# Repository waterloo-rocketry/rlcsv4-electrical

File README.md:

# Remote Launch Control System V4

### Towerside Boards:

- **ground_launch_sequencer_board** Ground Launch Sequencer Board
- **relay_board** Relay Board, Used for valve actuation, ignition and tank heating

### Clientside Boards:

- **clientside_board** Clientside Board

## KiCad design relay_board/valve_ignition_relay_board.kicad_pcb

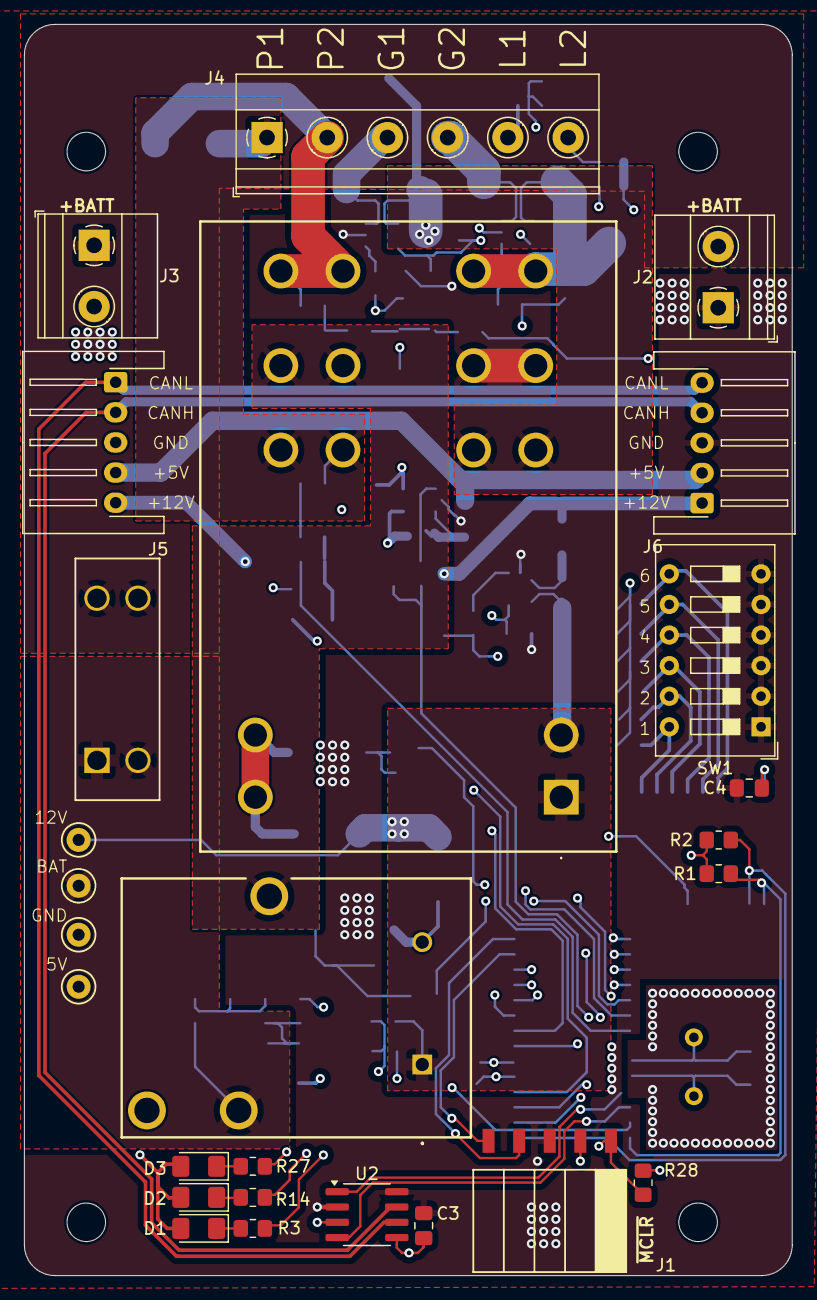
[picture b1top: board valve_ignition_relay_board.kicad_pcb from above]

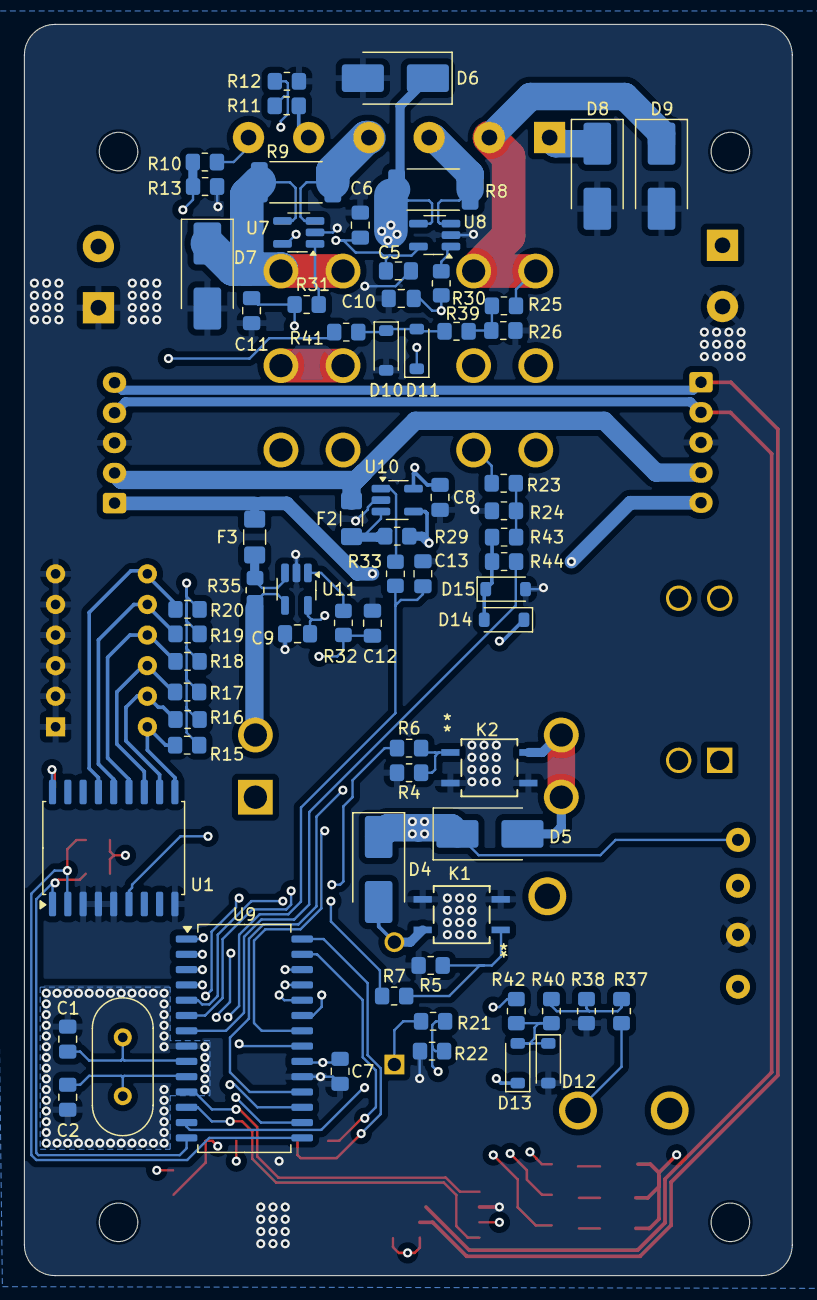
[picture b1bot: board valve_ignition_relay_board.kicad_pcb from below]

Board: 4 copper layers, 63.8 x 103.9 mm, 100 parts (70 on the bottom side), 68 nets.

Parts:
C1, C2: 27pF; C_0805_2012Metric_Pad1.18x1.45mm_HandSolder
C3: 10uF; C_0805_2012Metric_Pad1.18x1.45mm_HandSolder
C4, C5, C6, C7, C8, C9: 0.1uF; C_0805_2012Metric_Pad1.18x1.45mm_HandSolder
C10, C11, C12, C13: 1.6nF; C_0805_2012Metric_Pad1.18x1.45mm_HandSolder
D1: RED; LED_1206_3216Metric_Pad1.42x1.75mm_HandSolder
D2: BLUE; LED_1206_3216Metric_Pad1.42x1.75mm_HandSolder
D3: WHITE; LED_1206_3216Metric_Pad1.42x1.75mm_HandSolder
D4, D5, D6, D7, D8, D9: STPS2L25U; D_SMB_Handsoldering
D10, D11, D12, D13, D14, D15: 1N5819W; D_SOD-123
F1: 30A; 3557-10_KEY
F2: 150mA; Fuse_1206_3216Metric_Pad1.42x1.75mm_HandSolder
F3: 200mA; Fuse_1206_3216Metric_Pad1.42x1.75mm_HandSolder
H1, H2, H3, H4: MountingHole; MountingHole_3.2mm_M3
J1: Programming Header; PinSocket_5x2.54_SMD_90deg_952-3198-1-ND
J2, J3: ACT_PWR; TerminalBlock_Phoenix_MKDS-1,5-2-5.08_1x02_P5.08mm_Horizont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
J4: Actuator; TerminalBlock_Phoenix_MKDS-1,5-6_1x06_P5.00mm_Horizontal
J5: CAN Connector Left; JST_XH_S5B-XH-A-1_1x05_P2.50mm_Horizontal
J6: CAN Connector Right; JST_XH_S5B-XH-A-1_1x05_P2.50mm_Horizontal
K1, K2: PS2702-1-F3-A; SO4_PS2702-1_REN
K3: T9GV1L14-12; T9GV1L1412
K4: T92S11D12-12; T92S11D1212
R1, R2, R4, R5, R12, R13, R15, R16, R17, R18, R19, R20, R22, R24, R26, R28, R38, R41, R42, R44: 10K; R_0805_2012Metric_Pad1.20x1.40mm_HandSolder
R3: 150R; R_0805_2012Metric_Pad1.20x1.40mm_HandSolder
R6, R7: 220R; R_0805_2012Metric_Pad1.20x1.40mm_HandSolder
R8, R9: 0.001R; R_2512_6332Metric_Pad1.40x3.35mm_HandSolder
R10, R11, R23, R25, R37: 56K; R_0805_2012Metric_Pad1.20x1.40mm_HandSolder
R14, R27: 100R; R_0805_2012Metric_Pad1.20x1.40mm_HandSolder
R21: 20K; R_0805_2012Metric_Pad1.20x1.40mm_HandSolder
R29: 0.25R; R_0805_2012Metric_Pad1.20x1.40mm_HandSolder
R30, R31, R32, R33: 500R; R_0805_2012Metric_Pad1.20x1.40mm_HandSolder
R35: 0.6R; R_0805_2012Metric_Pad1.20x1.40mm_HandSolder
R39, R40, R43: 47R; R_0805_2012Metric_Pad1.20x1.40mm_HandSolder
SW1: SW_DIP_x06; SW_DIP_SPSTx06_Slide_9.78x17.42mm_W7.62mm_P2.54mm
TP1, TP2, TP3: TestPoint; TestPoint_Keystone_5000-5004_Miniature
TP4: Actuator PWR; TestPoint_Keystone_5000-5004_Miniature
U1: MCP23008; SOIC-18W_7.5x11.6mm_P1.27mm
U2: MCP2562; SOIC-8_3.9x4.9mm_P1.27mm
U7, U8, U10, U11: INA180A3; SOT-23-5_HandSoldering
U9: PIC18F26K83; SOIC-28W_7.5x18.7mm_P1.27mm
Y1: 12 MHz; Crystal_HC49-4H_Vertical

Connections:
+5V: C3.1, C4.1, C5.1, C6.1, C7.1, C8.1, C9.1, D1.2 (A), D2.2 (A), D3.2 (A), D11.1 (K), D13.1 (K), D14.1 (K), J1.2, R1.1, R2.1, R15.1, R16.1, R17.1, R18.1, R19.1, R20.1, R28.1, R29.2, TP2.1, U1.18 (VDD), U2.3 (VDD), U2.5 (VIO), U7.5 (VS), U8.5 (VS), U9.20 (VDD), U10.4 (IN-), U10.5 (VS), U11.5 (VS)
+12V: D4.1 (K), D5.1 (K), K3.1 (COIL_1), K4.1 (COIL_1), K4.2 (COIL_2), R21.1, R35.2, TP3.1, U11.4 (IN-)
+BATT: F1.1, K3.5 (NO), R37.2, TP4.1
/DipSwitch/CANH: J5.2, J6.4, U2.7 (CANH)
/DipSwitch/CANL: J5.1, J6.5, U2.6 (CANL)
/DipSwitch/CAN_RX: U2.4 (RXD), U9.12 (RC1)
/DipSwitch/CAN_TX: U2.1 (TXD), U9.11 (RC0)
/DipSwitch/CURRSENSE_IN5V: C13.2, R33.1, U9.21 (RB0)
/DipSwitch/CURRSENSE_IN12V: C12.2, R32.1, U9.22 (RB1)
/DipSwitch/CURR_SENSE_1: C10.2, R30.1, U9.18 (RC7)
/DipSwitch/CURR_SENSE_2: C11.2, R31.1, U9.16 (RC5)
/DipSwitch/DIP_1: R15.2, SW1.12, U1.10 (GP0)
/DipSwitch/DIP_2: R16.2, SW1.11, U1.11 (GP1)
/DipSwitch/DIP_3: R17.2, SW1.10, U1.12 (GP2)
/DipSwitch/DIP_4: R18.2, SW1.9, U1.13 (GP3)
/DipSwitch/DIP_5: R19.2, SW1.8, U1.14 (GP4)
/DipSwitch/DIP_6: R20.2, SW1.7, U1.15 (GP5)
/DipSwitch/ICSPCLK: J1.5, U9.27 (RB6/ICSPCLK)
/DipSwitch/ICSPDAT: J1.4, U9.28 (RB7/ICSPDAT)
/DipSwitch/LIM_1: R11.2, R12.1, U9.26 (RB5)
/DipSwitch/LIM_2: R10.1, R13.2, U9.25 (RB4)
/DipSwitch/OSC1: C1.2, U9.9 (RA7/OSC1), Y1.2
/DipSwitch/OSC2: C2.2, U9.10 (RA6/OSC2), Y1.1
/DipSwitch/POWER: R7.1, U9.5 (RA3)
/DipSwitch/RESET: U1.6 (~RESET), U9.24 (RB3)
/DipSwitch/SCL: R1.2, U1.1 (SCL), U9.14 (RC3)
/DipSwitch/SDA: R2.2, U1.2 (SDA), U9.15 (RC4)
/DipSwitch/SELECT: R6.1, U9.6 (RA4)
/DipSwitch/VSENSE_12V: R21.2, R22.2, U9.13 (RC2)
/DipSwitch/VSENSE_BATTERY: R37.1, R38.2, R40.2
/DipSwitch/VSENSE_OUTPUT1: R23.2, R24.1, R43.1
/DipSwitch/VSENSE_OUTPUT2: R25.1, R26.2, R39.2
/DipSwitch/~MCLR: J1.1, R28.2, U9.1 (~MCLR)
/Relay/G1: J4.3, R8.2, U8.3 (IN+)
/Relay/G2: J4.4, R9.2, U7.3 (IN+)
/Relay/P1: D8.1 (K), J4.1, K4.31 (NC_1), K4.32 (NC_2), R23.1
/Relay/P2: D9.1 (K), J4.2, K4.21 (NO_1), K4.22 (NO_2), R25.2
/Relay/T92S11D12-12/COM1: K3.3 (COM), K4.41 (COM_1), K4.42 (COM_2)
/Relay/T92S11D12-12/COUT: D5.2 (A), K2.4, K4.11 (COIL_3), K4.12 (COIL_4)
/Relay/T92S11D12-12/NC2: D6.1 (K), K4.71 (NC_3), K4.72 (NC_4), R8.1, U8.4 (IN-)
/Relay/T92S11D12-12/NO2: D7.1 (K), K4.61 (NO_3), K4.62 (NO_4), R9.1, U7.4 (IN-)
GND: C1.1, C2.1, C3.2, C4.2, C5.2, C6.2, C7.2, C8.2, C9.2, C10.1, C11.1, C12.1, C13.1, D6.2 (A), D7.2 (A), D8.2 (A), D9.2 (A), D10.2 (A), D12.2 (A), D15.2 (A), J1.3, J2.1, J3.2, J5.3, J6.3, K1.2, K1.3, K2.2, K2.3, K4.81 (COM_3), K4.82 (COM_4), R4.2, R5.2, R12.2, R13.1, R22.1, R24.2, R26.1, R38.1, SW1.1, SW1.2, SW1.3, SW1.4, SW1.5, SW1.6, TP1.1, U1.3 (A2), U1.4 (A1), U1.5 (A0), U1.9 (VSS), U2.2 (VSS), U2.8 (STBY), U7.2 (GND), U8.2 (GND), U9.8 (VSS), U9.19 (VSS), U10.2 (GND), U11.2 (GND)
unnamed: D1.1 (K), R3.1
unnamed: D2.1 (K), R14.1
unnamed: D3.1 (K), R27.1
unnamed: D4.2 (A), K1.4, K3.2 (COIL_2)
unnamed: D10.1 (K), D11.2 (A), R39.1, R41.2
unnamed: D12.1 (K), D13.2 (A), R40.1, R42.2
unnamed: D14.2 (A), D15.1 (K), R43.2, R44.1
unnamed: F1.2, J2.2, J3.1
unnamed: J4.5, R11.1
unnamed: J4.6, R10.2
unnamed: F2.2, J5.4, J6.2
unnamed: F3.2, J5.5, J6.1
unnamed: K1.1, R5.1, R7.2
unnamed: K2.1, R4.1, R6.2
unnamed: R31.2, U7.1 (VO)
unnamed: R30.2, U8.1 (VO)
unnamed: R27.2, U9.2 (RA0)
unnamed: R14.2, U9.3 (RA1)
unnamed: R3.2, U9.4 (RA2)
unnamed: R44.2, U9.7 (RA5)
unnamed: R42.1, U9.23 (RB2)
unnamed: R41.1, U9.17 (RC6)
unnamed: F2.1, R29.1, U10.3 (IN+)
unnamed: R33.2, U10.1 (VO)
unnamed: F3.1, R35.1, U11.3 (IN+)
unnamed: R32.2, U11.1 (VO)

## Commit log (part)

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2025-01-28 Initial Commit
    Add README
2025-01-31 Add Rocketry KiCAD footprint library
2025-02-07 Add .gitignore
2025-02-07 Add relay board
2025-03-11 Replaced MOSFETs with optoisolators
2025-03-11 Added IO Expander and moved dip switch
2025-03-11 Added NC to extra pins
2025-03-11 Valve Ignition Relay - ready for review 1
2025-03-11 Added 4 new signals to the microcontroller
2025-03-11 Changed Folder Name maybe?
2025-03-11 rename relay board folder
2025-03-18 Update README (#1)
2025-03-18 Changed to Hierarchical labels and added reverse voltage protection. Still need to do resistor math for voltage protection.
2025-03-18 Initial GLS schematics
2025-03-18 Initial clientside board schematics
2025-03-20 Cleanup Power and Ethernet Sheet
2025-03-20 Finished Reverse Voltage Math, added labels
2025-11-29 Update kicad-footprints submodule to latest main
2025-11-29 Update kicad-footprints submodule to latest main (#5)
2025-11-29 requested changes 1
2025-11-29 Silkscreen extras
2025-11-29 tidy up traces, add board name silkscreen
2025-11-29 add team logo
2025-11-29 lowpass current sense; move power traces to FCu
2025-11-29 Push JSTs to board edge
2025-11-29 fix symbols; routing v1
2025-11-29 Add untracked files; fix excess sym libs
